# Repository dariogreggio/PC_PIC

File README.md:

# PC_PIC
a full computer made with Microchip PICs, featuring *everything*

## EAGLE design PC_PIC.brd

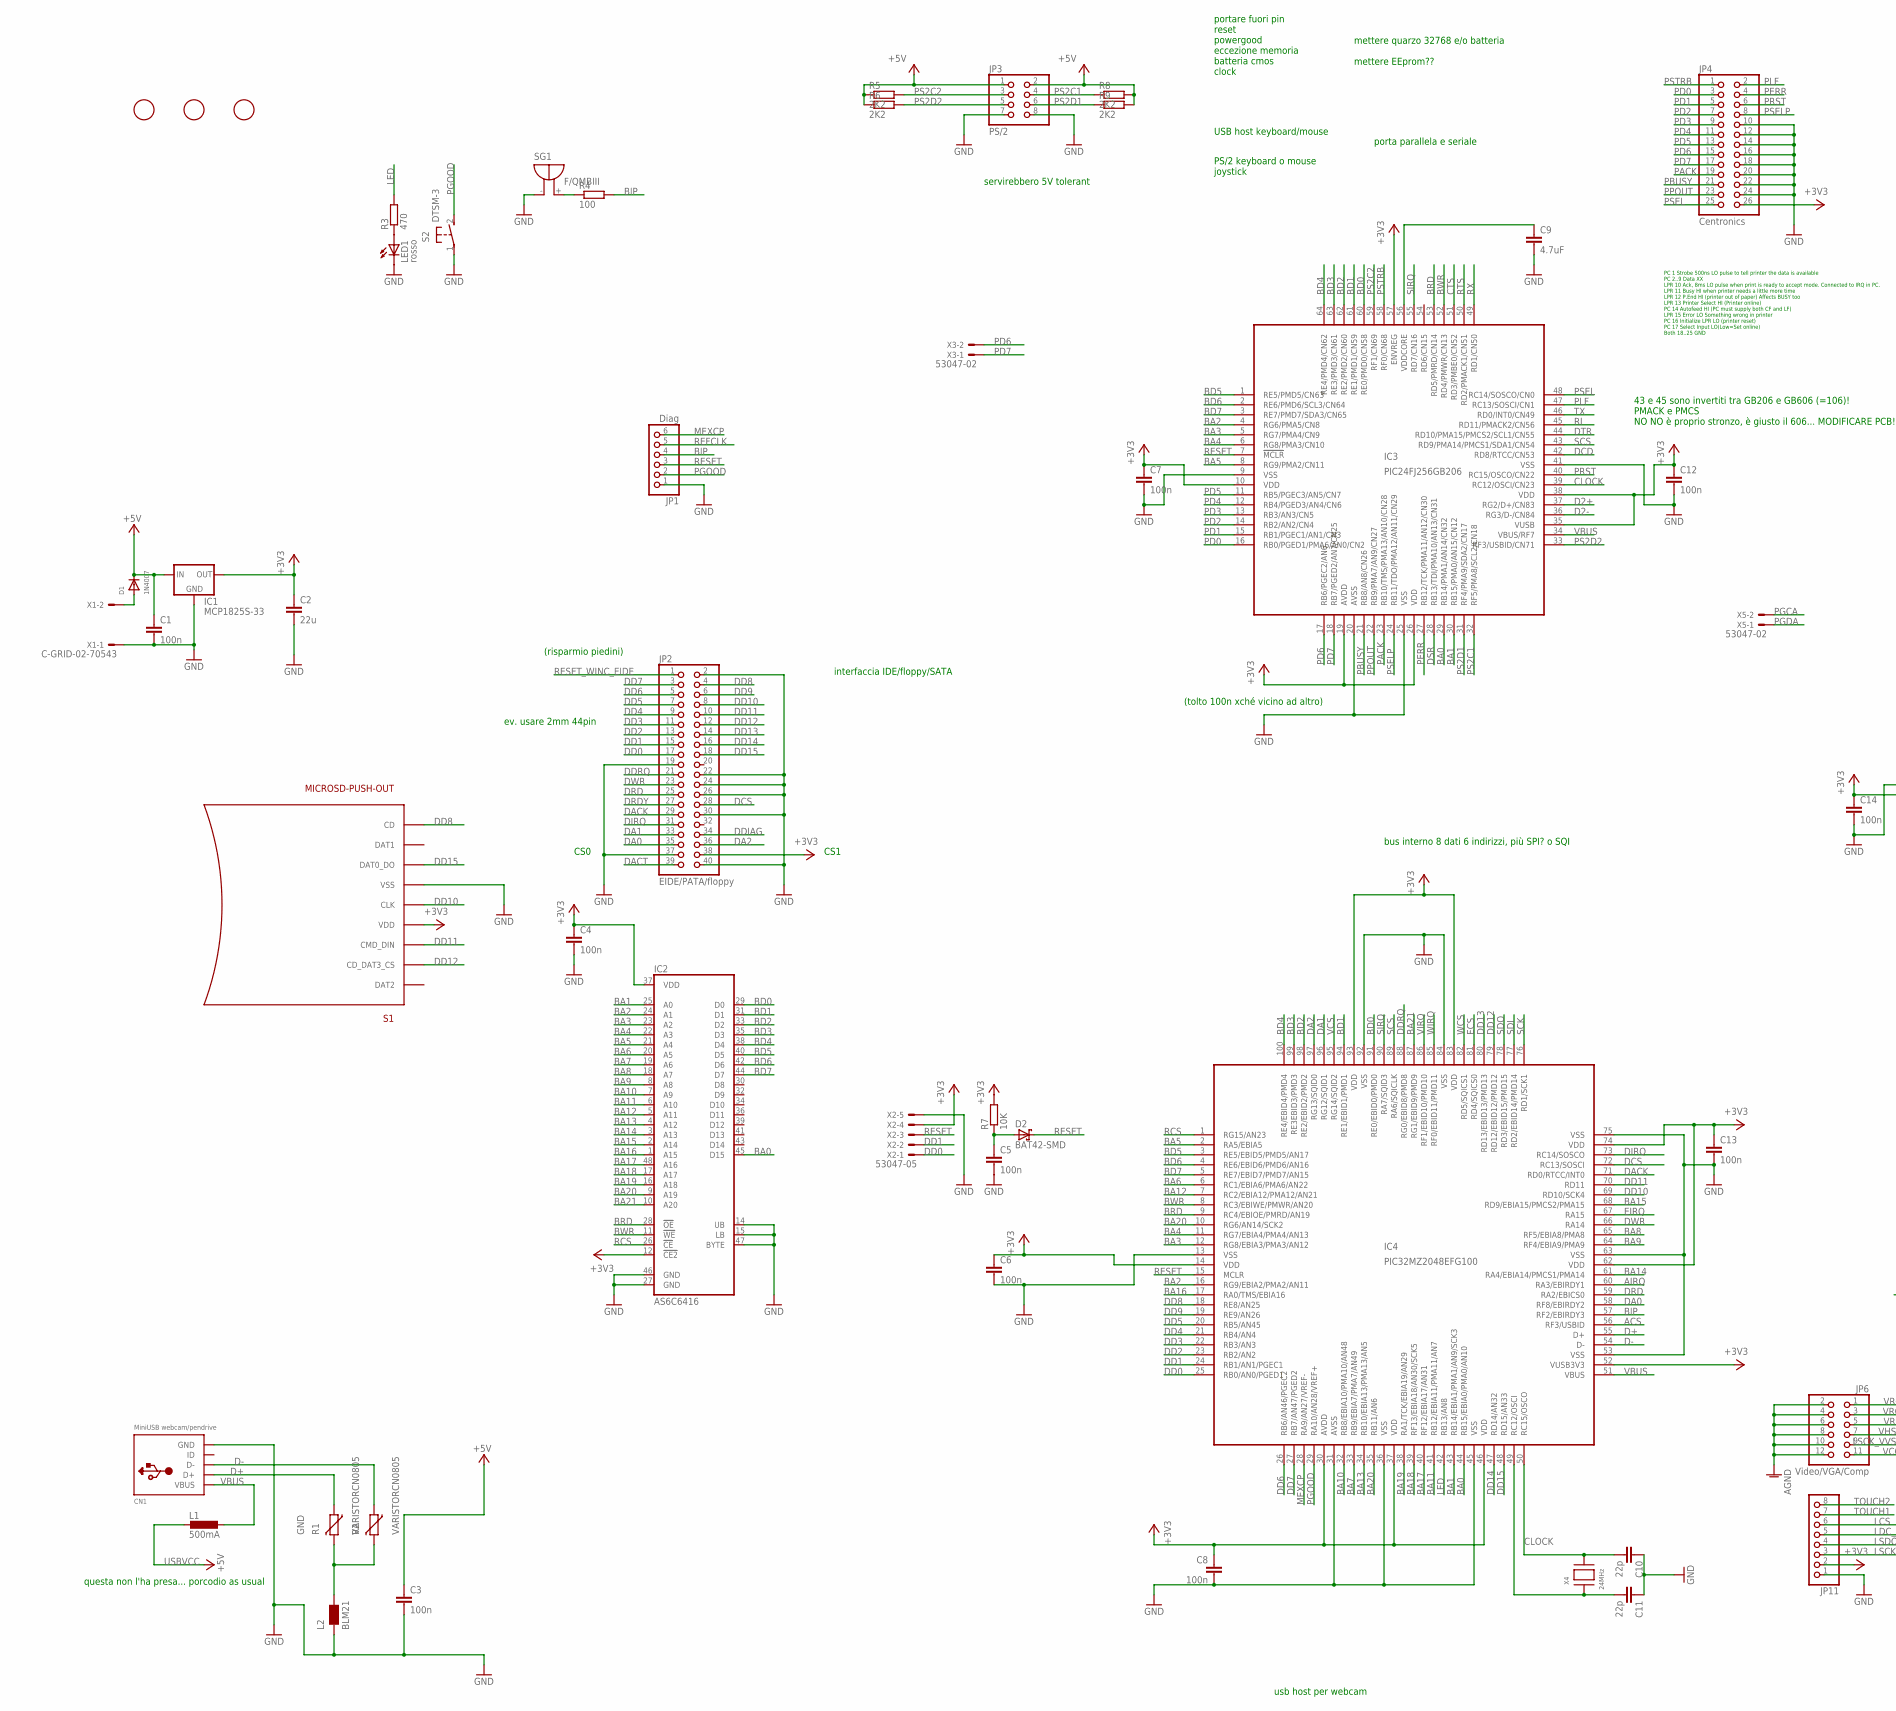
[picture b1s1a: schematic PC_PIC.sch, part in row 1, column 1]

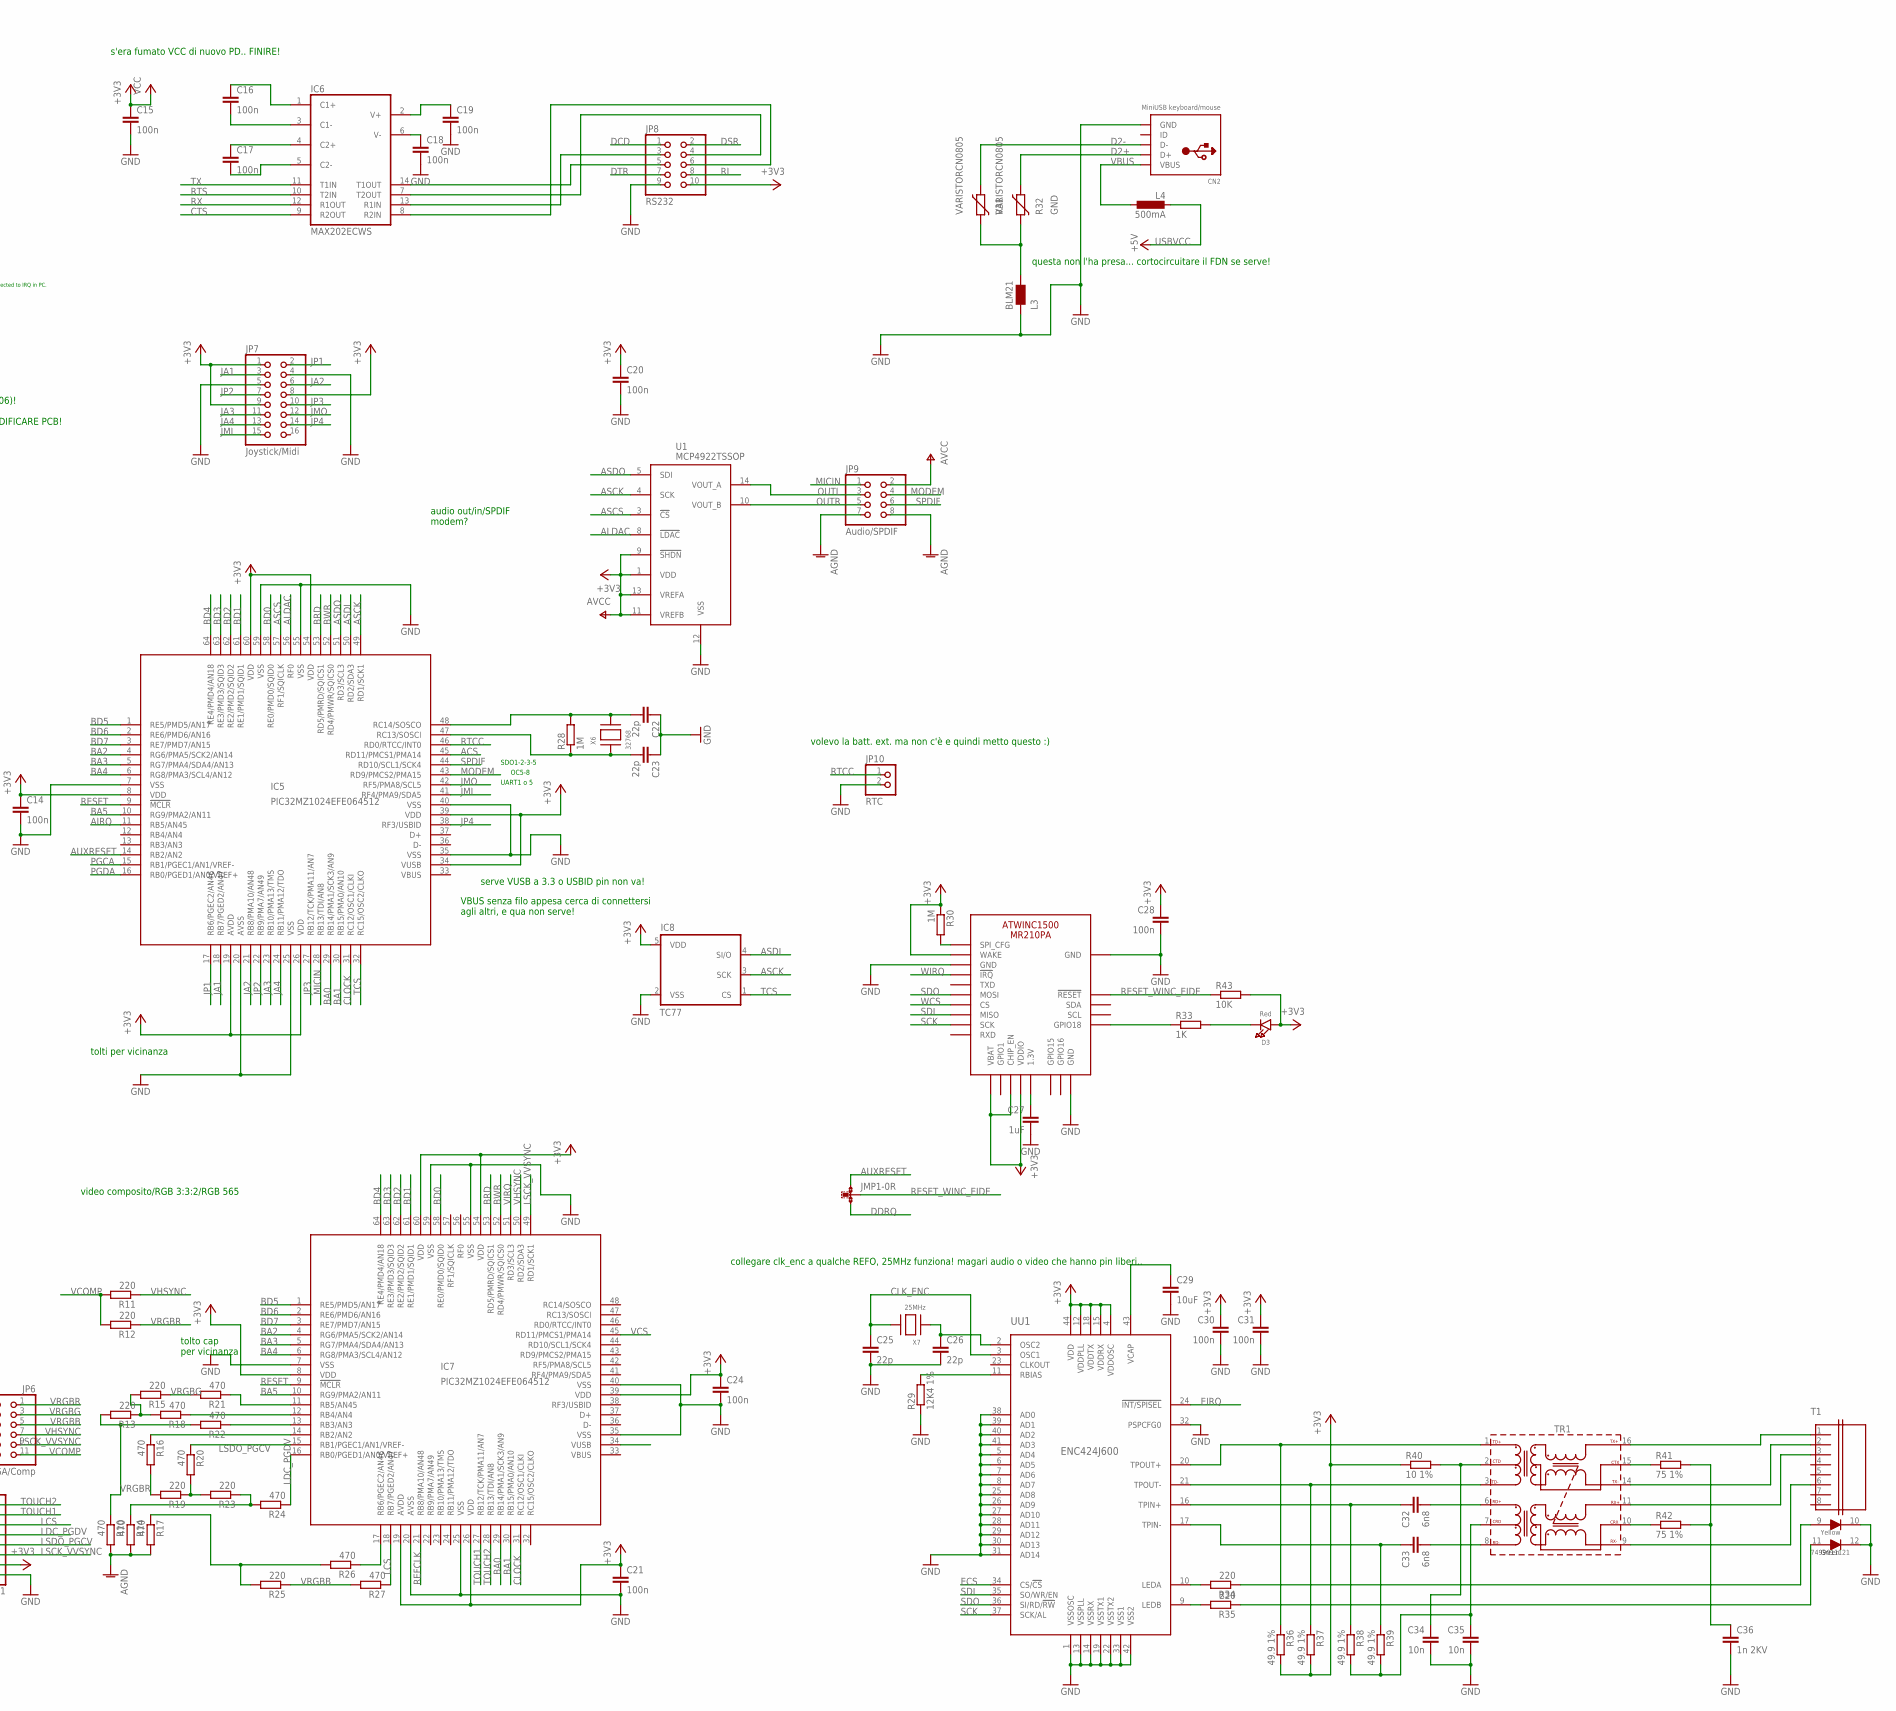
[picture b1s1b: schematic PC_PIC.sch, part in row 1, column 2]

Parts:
C1, C3, C4, C5, C6, C7, C8, C12, C13, C14, C15, C16, C17, C18, C19, C20, C21, C24, C28, C30, C31: 100n; C0805
C2: 22u; C1206
C9: 4.7uF; C1206
C10, C11, C22, C23, C25, C26: 22p; C0805
C27: 1uF; C0805
C29: 10uF; C1206
C32, C33: 6n8; C0805
C34, C35: 10n; C0805
C36: 1n 2KV; C1206
CN1: MiniUSB webcam/pendrive; USB-MINIB
CN2: MiniUSB keyboard/mouse; USB-MINIB
D1: 1N4007; SMADIODE
D2: BAT42-SMD; DO214AC
D3: Red; CHIPLED_0805_NOOUTLINE
F1, F2, F3: FIDUCIAL; FIDUCIAL_1MM
IC1: MCP1825S-33; SOT223
IC2: AS6C6416; TSOP48
IC3: PIC24FJ256GB206; TQFP64-10X10
IC4: PIC32MZ2048EFG100; TQFP100-14X14
IC5, IC7: PIC32MZ1024EFE064512; TQFP64-10X10
IC6: MAX202ECWS; SO16
IC8: TC77; SOT23-5L
JMP1: 0R-JUMPC; C0R-JMP
JP1: Diag; 1X06
JP2: EIDE/PATA/floppy; 2X20
JP3: PS/2; 2X04
JP4: Centronics; 2X13
JP6: Video/VGA/Comp; 2X06
JP7: Joystick/Midi; 2X08
JP8: RS232; 2X05
JP9: Audio/SPDIF; 2X04
JP10: RTC; 1X02
JP11: PINHD-1X08_2.54; 1X08
L1, L4: 500mA; L1812
L2, L3: BLM21; 0805
LED1: rosso; CHIPLED_0805
R1, R2, R31, R32: VARISTORCN0805; CT/CN0805
R3, R10, R14, R16, R17, R18, R20, R21, R22, R24, R26, R27: 470; R0805
R4: 100; R0805
R5, R6, R8, R9: 2K2; R0805
R7, R43: 10K; R0805
R11, R12, R13, R15, R19, R23, R25, R34, R35: 220; R0805
R28, R30: 1M; R0805
R29: 12K4 1%; R0805
R33: 1K; R0805
R36, R37, R38, R39: 49.9 1%; R0805
R40: 10 1%; R0805
R41, R42: 75 1%; R0805
S1: MICROSD-PUSH-OUT
S2: DTSM-3
SG1: F/QMBIII
T1: 7499011121; 01LAN_RJ45_10/00_Y-G_STD
TR1: WE-LAN-10/100-BASE-T,POE,749013011; 749013011
U1: MCP4922TSSOP; TSSOP14
UU1: ENC424J600; TQFP-44
X1: C-GRID-02-70543; 70543-02
X2: 53047-05
X3, X5: 53047-02
X4: 24MHz; NX5032
X6: 32768; XTAL3215
X7: 25MHz; NX5032
X8: ATWINC1500_MR210PB; ATWINC1500_MR210PA

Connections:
+3V3: C2.1, C4.1, C6.1, C7.1, C8.1, C12.1, C13.1, C14.1, C15.1, C20.1, C21.1, C24.1, C28.1, C30.1, C31.1, D3.A, IC1.3 (OUT), IC2.12 (!CE2), IC2.37 (VDD), IC3.10 (VDD), IC3.19 (AVDD), IC3.26 (VDD), IC3.35 (VUSB), IC3.38 (VDD), IC3.57 (ENVREG), IC4.14 (VDD), IC4.30 (AVDD), IC4.37 (VDD), IC4.46 (VDD), IC4.52 (VUSB3V3), IC4.62 (VDD), IC4.74 (VDD), IC4.83 (VDD), IC4.93 (VDD), IC5.8 (VDD), IC5.19 (AVDD), IC5.26 (VDD), IC5.34 (VUSB), IC5.39 (VDD), IC5.54 (VDD), IC5.60 (VDD), IC7.8 (VDD), IC7.19 (AVDD), IC7.26 (VDD), IC7.39 (VDD), IC7.54 (VDD), IC7.60 (VDD), IC8.5 (VDD), JP2.38, JP4.26, JP7.1, JP7.8, JP7.9, JP8.10, JP9.2, JP11.2, R7.2, R30.1, R36.2, R37.2, R40.1, R43.2, S1.4 (VDD), U1.1 (VDD), U1.9 (!SHDN), U1.11 (VREFB), U1.13 (VREFA), UU1.4 (VDDOSC), UU1.12 (VDDPLL), UU1.15 (VDDRX), UU1.18 (VDDTX), UU1.44 (VDD), X2.4, X8.J11 (WAKE), X8.J20 (VBAT), X8.J22 (CHIP_EN), X8.J23 (VDDIO)
+5V: C1.1, C3.1, D1.C, IC1.1 (IN), JP3.1, JP3.2, R5.1, R6.1, R8.2, R9.2
ACS: IC4.56 (RF3/USBID), IC5.45 (RD11/PMCS1/PMA14)
AIRQ: IC4.60 (RA3/EBIRDY1), IC5.11 (RB5/AN45)
ALDAC: IC5.56 (RF0), U1.8 (!LDAC)
ASCK: IC5.49 (RD1/SCK1), IC8.3 (SCK), U1.4 (SCK)
ASCS: IC5.57 (RF1/SQICLK), U1.3 (!CS)
ASDI: IC5.50 (RD2/SDA3), IC8.4 (SI/O)
ASDO: IC5.51 (RD3/SCL3), U1.5 (SDI)
AUXRESET: IC5.14 (RB2/AN2), JMP1.1
BA0: IC2.45 (D15), IC3.29 (RB14/PMA1/AN14/CN32), IC4.44 (RB15/EBIA0/PMA0/AN10), IC5.29 (RB14/PMA1/SCK3/AN9), IC7.29 (RB14/PMA1/SCK3/AN9)
BA1: IC2.25 (A0), IC3.30 (RB15/PMA0/AN15/CN12), IC4.43 (RB14/EBIA1/PMA1/AN9/SCK3), IC5.30 (RB15/PMA0/AN10), IC7.30 (RB15/PMA0/AN10)
BA2: IC2.24 (A1), IC3.4 (RG6/PMA5/CN8), IC4.16 (RG9/EBIA2/PMA2/AN11), IC5.4 (RG6/PMA5/SCK2/AN14), IC7.4 (RG6/PMA5/SCK2/AN14)
BA3: IC2.23 (A2), IC3.5 (RG7/PMA4/CN9), IC4.12 (RG8/EBIA3/PMA3/AN12), IC5.5 (RG7/PMA4/SDA4/AN13), IC7.5 (RG7/PMA4/SDA4/AN13)
BA4: IC2.22 (A3), IC3.6 (RG8/PMA3/CN10), IC4.11 (RG7/EBIA4/PMA4/AN13), IC5.6 (RG8/PMA3/SCL4/AN12), IC7.6 (RG8/PMA3/SCL4/AN12)
BA5: IC2.21 (A4), IC3.8 (RG9/PMA2/CN11), IC4.2 (RA5/EBIA5), IC5.10 (RG9/PMA2/AN11), IC7.10 (RG9/PMA2/AN11)
BA6: IC2.20 (A5), IC4.6 (RC1/EBIA6/PMA6/AN22)
BA7: IC2.19 (A6), IC4.33 (RB9/EBIA7/PMA7/AN49)
BA8: IC2.18 (A7), IC4.65 (RF5/EBIA8/PMA8)
BA9: IC2.8 (A8), IC4.64 (RF4/EBIA9/PMA9)
BA10: IC2.7 (A9), IC4.32 (RB8/EBIA10/PMA10/AN48)
BA11: IC2.6 (A10), IC4.41 (RB12/EBIA11/PMA11/AN7)
BA12: IC2.5 (A11), IC4.7 (RC2/EBIA12/PMA12/AN21)
BA13: IC2.4 (A12), IC4.34 (RB10/EBIA13/PMA13/AN5)
BA14: IC2.3 (A13), IC4.61 (RA4/EBIA14/PMCS1/PMA14)
BA15: IC2.2 (A14), IC4.68 (RD9/EBIA15/PMCS2/PMA15)
BA16: IC2.1 (A15), IC4.17 (RA0/TMS/EBIA16)
BA17: IC2.48 (A16), IC4.40 (RF12/EBIA17/AN31)
BA18: IC2.17 (A17), IC4.39 (RF13/EBIA18/AN30/SCK5)
BA19: IC2.16 (A18), IC4.38 (RA1/TCK/EBIA19/AN29)
BA20: IC2.9 (A19), IC4.10 (RG6/AN14/SCK2), IC4.35 (RB11/AN6)
BA21: IC2.10 (A20), IC4.87 (RG1/EBID9/PMD9)
BD0: IC2.29 (D0), IC3.60 (RE0/PMD0/CN58), IC4.91 (RE0/EBID0/PMD0), IC5.58 (RE0/PMD0/SQID0), IC7.58 (RE0/PMD0/SQID0)
BD1: IC2.31 (D1), IC3.61 (RE1/PMD1/CN59), IC4.94 (RE1/EBID1/PMD1), IC5.61 (RE1/PMD1/SQID1), IC7.61 (RE1/PMD1/SQID1)
BD2: IC2.33 (D2), IC3.62 (RE2/PMD2/CN60), IC4.98 (RE2/EBID2/PMD2), IC5.62 (RE2/PMD2/SQID2), IC7.62 (RE2/PMD2/SQID2)
BD3: IC2.35 (D3), IC3.63 (RE3/PMD3/CN61), IC4.99 (RE3EBID3/PMD3), IC5.63 (RE3/PMD3/SQID3), IC7.63 (RE3/PMD3/SQID3)
BD4: IC2.38 (D4), IC3.64 (RE4/PMD4/CN62), IC4.100 (RE4/EBID4/PMD4), IC5.64 (RE4/PMD4/AN18), IC7.64 (RE4/PMD4/AN18)
BD5: IC2.40 (D5), IC3.1 (RE5/PMD5/CN63), IC4.3 (RE5/EBID5/PMD5/AN17), IC5.1 (RE5/PMD5/AN17), IC7.1 (RE5/PMD5/AN17)
BD6: IC2.42 (D6), IC3.2 (RE6/PMD6/SCL3/CN64), IC4.4 (RE6/EBID6/PMD6/AN16), IC5.2 (RE6/PMD6/AN16), IC7.2 (RE6/PMD6/AN16)
BD7: IC2.44 (D7), IC3.3 (RE7/PMD7/SDA3/CN65), IC4.5 (RE7/EBID7/PMD7/AN15), IC5.3 (RE7/PMD7/AN15), IC7.3 (RE7/PMD7/AN15)
BIP: IC4.57 (RF2/EBIRDY3), JP1.4, R4.2
BRD: IC2.28 (!OE), IC3.53 (RD5/PMRD/CN14), IC4.9 (RC4/EBIOE/PMRD/AN19), IC5.53 (RD5/PMRD/SQICS1), IC7.53 (RD5/PMRD/SQICS1)
BWR: IC2.11 (!WE), IC3.52 (RD4/PMWR/CN13), IC4.8 (RC3/EBIWE/PMWR/AN20), IC5.52 (RD4/PMWR/SQICS0), IC7.52 (RD4/PMWR/SQICS0)
CLK_ENC: C25.1, UU1.3 (OSC1), X7.P$2
CLOCK: C10.2, IC3.39 (RC12/OSCI/CN23), IC4.50 (RC15/OSCO), IC5.31 (RC12/OSC1/CLKI), IC7.31 (RC12/OSC1/CLKI), X4.P$2
CTS: IC3.51 (RD3/PMBE0/CN52), IC6.9 (R2OUT)
D2+: CN2.D+, IC3.37 (RG2/D+/CN83), R32.1
D2-: CN2.D-, IC3.36 (RG3/D-/CN84), R31.1
D+: CN1.D+, IC4.55 (D+), R1.1
D-: CN1.D-, IC4.54 (D-), R2.1
DA0: IC4.58 (RF8/EBIRDY2), JP2.35
DA1: IC4.96 (RG12/SQID1), JP2.33
DA2: IC4.97 (RG13/SQID0), JP2.36
DACK: IC4.71 (RD0/RTCC/INT0), JP2.29
DACT: JP2.39
DCD: IC3.42 (RD8/RTCC/CN53), JP8.1
DCS: IC4.72 (RC13/SOSCI), JP2.28
DD0: IC4.25 (RB0/AN0/PGED1), JP2.17, X2.1
DD1: IC4.24 (RB1/AN1/PGEC1), JP2.15, X2.2
DD2: IC4.23 (RB2/AN2), JP2.13
DD3: IC4.22 (RB3/AN3), JP2.11
DD4: IC4.21 (RB4/AN4), JP2.9
DD5: IC4.20 (RB5/AN45), JP2.7
DD6: IC4.26 (RB6/AN46/PGEC2), JP2.5
DD7: IC4.27 (RB7/AN47/PGED2), JP2.3
DD8: IC4.18 (RE8/AN25), JP2.4, S1.CD
DD9: IC4.19 (RE9/AN26), JP2.6
DD10: IC4.69 (RD10/SCK4), JP2.8, S1.5 (CLK)
DD11: IC4.70 (RD11), JP2.10, S1.3 (CMD_DIN)
DD12: IC4.79 (RD12/EBID12/PMD12), JP2.12, S1.2 (CD_DAT3_CS)
DD13: IC4.80 (RD13/EBID13/PMD13), JP2.14
DD14: IC4.47 (RD14/AN32), JP2.16
DD15: IC4.48 (RD15/AN33), JP2.18, S1.7 (DAT0_DO)
DDIAG: JP2.34
DDRQ: IC4.88 (RG0/EBID8/PMD8), JMP1.3, JP2.21
DIRQ: IC4.73 (RC14/SOSCO), JP2.31
DRD: IC4.59 (RA2/EBICS0), JP2.25
DRDY: JP2.27
DSR: IC3.28 (RB13/TDI/PMA10/AN13/CN31), JP8.2
DTR: IC3.44 (RD10/PMA15/PMCS2/SCL1/CN55), JP8.7
DWR: IC4.66 (RA14), JP2.23
ECS: IC4.81 (RD4/SQICS0), UU1.34 (CS/!CS)
EIRQ: IC4.67 (RA15), UU1.24 (!INT/SPISEL)
GND: C1.2, C2.2, C3.2, C4.2, C5.2, C6.2, C7.2, C8.2, C9.2, C10.1, C11.1, C12.2, C13.2, C14.2, C15.2, C18.2, C19.2, C20.2, C21.2, C22.1, C23.1, C24.2, C25.2, C26.2, C27.2, C28.2, C29.2, C30.2, C31.2, C34.2, C35.2, C36.2, CN1.GND, CN2.GND, IC1.2 (GND), IC1.4 (GND), IC2.14 (UB), IC2.15 (LB), IC2.27 (GND), IC2.46 (GND), IC2.47 (BYTE), IC3.9 (VSS), IC3.20 (AVSS), IC3.25 (VSS), IC3.41 (VSS), IC4.13 (VSS), IC4.31 (AVSS), IC4.36 (VSS), IC4.45 (VSS), IC4.53 (VSS), IC4.63 (VSS), IC4.75 (VSS), IC4.84 (VSS), IC4.92 (VSS), IC5.7 (VSS), IC5.20 (AVSS), IC5.25 (VSS), IC5.35 (VSS), IC5.40 (VSS), IC5.55 (VSS), IC5.59 (VSS), IC6.15 (GND), IC7.7 (VSS), IC7.20 (AVSS), IC7.25 (VSS), IC7.35 (VSS), IC7.40 (VSS), IC7.55 (VSS), IC7.59 (VSS), IC8.2 (VSS), JP1.1, JP2.2, JP2.19, JP2.22, JP2.24, JP2.26, JP2.30, JP2.37, JP2.40, JP3.7, JP3.8, JP4.10, JP4.12, JP4.14, JP4.16, JP4.18, JP4.20, JP4.22, JP4.24, JP6.2, JP6.4, JP6.6, JP6.8, JP6.10, JP6.12, JP7.4, JP7.5, JP8.9, JP9.7, JP9.8, JP10.2, JP11.1, L2.1, L3.1, LED1.C, R10.2, R14.2, R17.2, R29.1, S1.6 (VSS), S1.G1 (VSS), S1.G2 (VSS), S1.G3 (VSS), S1.G4 (VSS), S2.1, SG1.- (+), T1.10, T1.12, U1.12 (VSS), UU1.1 (VSSOSC), UU1.5 (AD4), UU1.6 (AD5), UU1.7 (AD6), UU1.8 (AD7), UU1.13 (VSSPLL), UU1.14 (VSSRX), UU1.19 (VSSTX1), UU1.22 (VSSTX2), UU1.25 (AD8), UU1.26 (AD9), UU1.27 (AD10), UU1.28 (AD11), UU1.29 (AD12), UU1.30 (AD13), UU1.31 (AD14), UU1.32 (PSPCFG0), UU1.33 (VSS1), UU1.38 (AD0), UU1.39 (AD1), UU1.40 (AD2), UU1.41 (AD3), UU1.42 (VSS2), X1.1, X2.5, X8.J9 (GND), X8.J12 (GND), X8.J28 (GND), X8.MTGND (GND)
JA1: IC5.18 (RB7/PGED2/AN47), JP7.3
JA2: IC5.21 (RB8/PMA10/AN48), JP7.6
JA3: IC5.23 (RB10/PMA13/TMS), JP7.11
JA4: IC5.24 (RB11/PMA12/TDO), JP7.13
JMI: IC5.41 (RF4/PMA9/SDA5), JP7.15
JMO: IC5.42 (RF5/PMA8/SCL5), JP7.12
JP1: IC5.17 (RB6/PGEC2/AN46), JP7.2
JP2: IC5.22 (RB9/PMA7/AN49), JP7.7
JP3: IC5.27 (RB12/TCK/PMA11/AN7), JP7.10
JP4: IC5.38 (RF3/USBID), JP7.14
LCS: IC7.18 (RB7/PGED2/AN47), JP11.6, R27.1
LDC_PGDV: IC7.16 (RB0/PGED1/AN0/VREF+), JP11.5, R24.1
LED: IC4.42 (RB13/AN8), R3.2
LSCK_VVSYNC: IC7.49 (RD1/SCK1), JP6.9, JP11.3
LSDO_PGCV: IC7.15 (RB1/PGEC1/AN1/VREF-), JP11.4, R20.1
MEXCP: IC4.28 (RA9/AN27/VREF-), JP1.6
MICIN: IC5.28 (RB13/TDI/AN8), JP9.1
MODEM: IC5.43 (RD9/PMCS2/PMA15), JP9.4
unnamed: C32.2, TR1.6 (RD+)
unnamed: R36.1, TR1.1 (TD+), UU1.20 (TPOUT+)
unnamed: C16.2, IC6.3 (C1-)
unnamed: C5.1, D2.A, R7.1
unnamed: D1.A, X1.2
unnamed: LED1.A, R3.1
unnamed: C16.1, IC6.1 (C1+)
unnamed: R37.1, TR1.3 (TD-), UU1.21 (TPOUT-)
unnamed: R4.1, SG1.+ (-)
unnamed: C32.1, R38.1, UU1.16 (TPIN+)
unnamed: IC7.17 (RB6/PGEC2/AN46), R26.1
unnamed: C34.1, R40.2, TR1.2 (CTD)
unnamed: C33.1, R39.1, UU1.17 (TPIN-)
unnamed: C17.1, IC6.4 (C2+)
unnamed: IC7.14 (RB2/AN2), R16.1
unnamed: R33.1, X8.J1 (GPIO18)
unnamed: D3.C, R33.2
unnamed: IC7.11 (RB5/AN45), R21.1
unnamed: C11.2, IC4.49 (RC12/OSCI), X4.P$1
unnamed: C27.1, X8.J24 (1.3V)
unnamed: R30.2, X8.J10 (SPI_CFG)
unnamed: C26.1, UU1.2 (OSC2), X7.P$1
unnamed: IC7.12 (RB4/AN4), R18.1
unnamed: R29.2, UU1.11 (RBIAS)
unnamed: C17.2, IC6.5 (C2-)
unnamed: R35.1, T1.11
unnamed: C29.1, UU1.43 (VCAP)
unnamed: R34.2, UU1.10 (LEDA)
unnamed: R35.2, UU1.9 (LEDB)
unnamed: T1.1, TR1.16 (TX+)
unnamed: T1.2, TR1.14 (TX-)
unnamed: T1.3, TR1.11 (RX+)
unnamed: C19.1, IC6.2 (V+)
unnamed: C18.1, IC6.6 (V-)
unnamed: T1.6, TR1.9 (RX-)
unnamed: R34.1, T1.9
unnamed: IC6.14 (T1OUT), JP8.5
unnamed: IC6.7 (T2OUT), JP8.4
unnamed: C33.2, TR1.8 (RD-)
unnamed: C35.1, R38.2, R39.2, TR1.7 (CRD)
unnamed: R41.1, TR1.15 (CTX)
unnamed: R42.1, TR1.10 (CRX)
unnamed: C36.1, R41.2, R42.2
unnamed: IC6.13 (R1IN), JP8.3
unnamed: IC6.8 (R2IN), JP8.6
unnamed: C9.1, IC3.56 (VDDCORE)
unnamed: IC7.13 (RB3/AN3), R22.1
unnamed: R17.1, R25.2, R26.2
unnamed: R10.1, R13.2, R22.2
unnamed: R19.1, R20.2, R23.2
unnamed: R14.1, R23.1, R24.2
unnamed: R13.1, R15.2, R18.2
OUTL: JP9.3, U1.14 (VOUT_A)
OUTR: JP9.5, U1.10 (VOUT_B)
PACK: IC3.23 (RB10/TMS/PMA13/AN10/CN28), JP4.19
PBUSY: IC3.21 (RB8/AN8/CN26), JP4.21
PD0: IC3.16 (RB0/PGED1/PMA6/AN0/CN2), JP4.3
PD1: IC3.15 (RB1/PGEC1/AN1/CN3), JP4.5
PD2: IC3.14 (RB2/AN2/CN4), JP4.7
PD3: IC3.13 (RB3/AN3/CN5), JP4.9
PD4: IC3.12 (RB4/PGED3/AN4/CN6), JP4.11
PD5: IC3.11 (RB5/PGEC3/AN5/CN7), JP4.13
PD6: IC3.17 (RB6/PGEC2/AN6), JP4.15, X3.2
PD7: IC3.18 (RB7/PGED2/AN7/CN25), JP4.17, X3.1
PERR: IC3.27 (RB12/TCK/PMA11/AN12/CN30), JP4.4
PGCA: IC5.15 (RB1/PGEC1/AN1/VREF-), X5.2
PGDA: IC5.16 (RB0/PGED1/AN0/VREF+), X5.1
PGOOD: IC4.29 (RA10/AN28/VREF+), JP1.2, S2.2
PLF: IC3.47 (RC13/SOSCI/CN1), JP4.2
PPOUT: IC3.22 (RB9/PMA7/AN9/CN27), JP4.23
PRST: IC3.40 (RC15/OSCO/CN22), JP4.6
PS2C1: IC3.32 (RF5/PMA8/SCL2/CN18), JP3.4, R8.1
PS2C2: IC3.59 (RF1/CN69), JP3.3, R5.2
PS2D1: IC3.31 (RF4/PMA9/SDA2/CN17), JP3.6, R9.1
PS2D2: IC3.33 (RF3/USBID/CN71), JP3.5, R6.2
PSEL: IC3.48 (RC14/SOSCO/CN0), JP4.25
PSELP: IC3.24 (RB11/TDO/PMA12/AN11/CN29), JP4.8
PSTRB: IC3.58 (RF0/CN68), JP4.1
RCS: IC2.26 (!CE), IC4.1 (RG15/AN23)
REFCLK: IC7.21 (RB8/PMA10/AN48), JP1.5
RESET: D2.C, IC3.7 (!MCLR), IC4.15 (MCLR), IC5.9 (!MCLR), IC7.9 (!MCLR), JP1.3, X2.3
RESET_WINC_EIDE: JMP1.2, JP2.1, R43.1, X8.J4 (!RESET)
RI: IC3.45 (RD11/PMACK2/CN56), JP8.8
RTCC: IC5.46 (RD0/RTCC/INT0), JP10.1
RTS: IC3.50 (RD2/PMACK1/CN51), IC6.10 (T2IN)
RX: IC3.49 (RD1/CN50), IC6.12 (R1OUT)
SCK: IC4.76 (RD1/SCK1), UU1.37 (SCK/AL), X8.J18 (SCK)
SCS: IC3.43 (RD9/PMA14/PMCS1/SDA1/CN54), IC4.89 (RA6/SQICLK)
SDI: IC4.77 (RD2/EBID14/PMD14), UU1.35 (SO/WR/EN), X8.J17 (MISO)
SDO: IC4.78 (RD3/EBID15/PMD15), UU1.36 (SI/RD/!RW), X8.J15 (MOSI)
SIRQ: IC3.55 (RD7/CN16), IC4.90 (RA7/SQID3)
SOSCI: C23.2, IC5.47 (RC13/SOSCI), R28.1, X6.P$1
SOSCO: C22.2, IC5.48 (RC14/SOSCO), R28.2, X6.P$2
SPDIF: IC5.44 (RD10/SCL1/SCK4), JP9.6
TCS: IC5.32 (RC15/OSC2/CLKO), IC8.1 (CS)
TOUCH1: IC7.27 (RB12/TCK/PMA11/AN7), JP11.7
TOUCH2: IC7.28 (RB13/TDI/AN8), JP11.8
TX: IC3.46 (RD0/INT0/CN49), IC6.11 (T1IN)
USBVCC: L1.2, L4.2
USHIELD: L2.2, R1.2, R2.2
USHIELD1: L3.2, R31.2, R32.2
VBUS: CN1.VBUS, CN2.VBUS, IC3.34 (VBUS/RF7), IC4.51 (VBUS), L1.1, L4.1
VCC: IC6.16 (VCC)
VCOMP: JP6.11, R11.2, R12.2
VCS: IC4.95 (RG14/SQID2), IC7.45 (RD11/PMCS1/PMA14)
VHSYNC: IC7.50 (RD2/SDA3), JP6.7, R11.1
VIRQ: IC4.86 (RF1/EBID10/PMD10), IC7.51 (RD3/SCL3)
VRGBB: JP6.5, R25.1, R27.2
VRGBG: JP6.3, R15.1, R21.2
VRGBR: JP6.1, R12.1, R16.2, R19.2
WCS: IC4.82 (RD5/SQICS1), X8.J16 (CS)
WIRQ: IC4.85 (RF0/EBID11/PMD11), X8.J13 (!IRQ)

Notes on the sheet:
questa non l'ha presa... porcodio as usual
video composito/RGB 3:3:2/RGB 565
usb host per webcam
USB host keyboard/mouse
PS/2 keyboard o mouse joystick
audio out/in/SPDIF modem?
interfaccia IDE/floppy/SATA
bus interno 8 dati 6 indirizzi, più SPI? o SQI
porta parallela e seriale
questa non l'ha presa... cortocircuitare il FDN se serve!
portare fuori pin reset powergood eccezione memoria batteria cmos clock
mettere quarzo 32768 e/o batteria mettere EEprom??
(risparmio piedini)
servirebbero 5V tolerant
PC 1 Strobe 500ns LO pulse to tell printer the data is available PC 2..9 Data XX LPR 10 Ack, 8ms LO pulse when print is ready to accept mode. Connected to IRQ in PC. LPR 11 Busy HI when printer needs a little more time LPR 12 P.End HI (printer out of paper) Affects BUSY too LPR 13 Printer Select HI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
volevo la batt. ext. ma non c'è e quindi metto questo :)
ev. usare 2mm 44pin
(tolto 100n xché vicino ad altro)
tolto cap per vicinanza
tolti per vicinanza
serve VUSB a 3.3 o USBID pin non va!
UART1 o 5
SDO1-2-3-5
OC5-8
CS1
CS0
s'era fumato VCC di nuovo PD.. FINIRE!
43 e 45 sono invertiti tra GB206 e GB606 (=106)! PMACK e PMCS NO NO è proprio stronzo, è giusto il 606... MODIFICARE PCB!
VBUS senza filo appesa cerca di connettersi agli altri, e qua non serve!
collegare clk_enc a qualche REFO, 25MHz funziona! magari audio o video che hanno pin liberi..

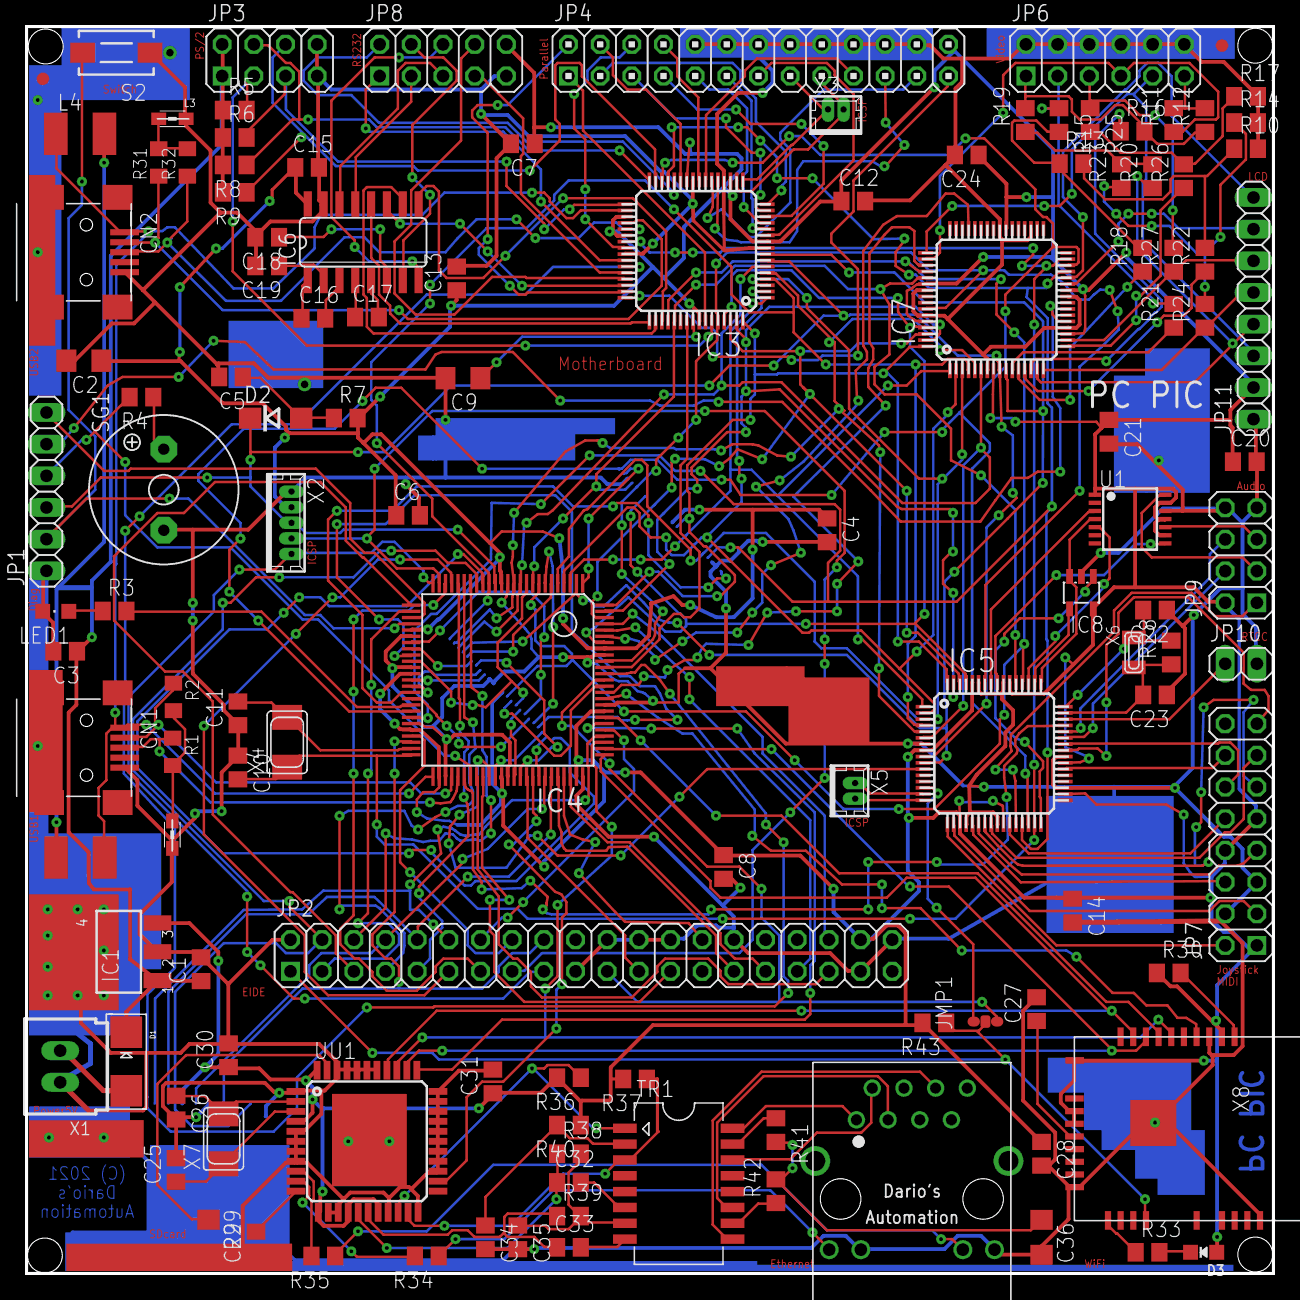
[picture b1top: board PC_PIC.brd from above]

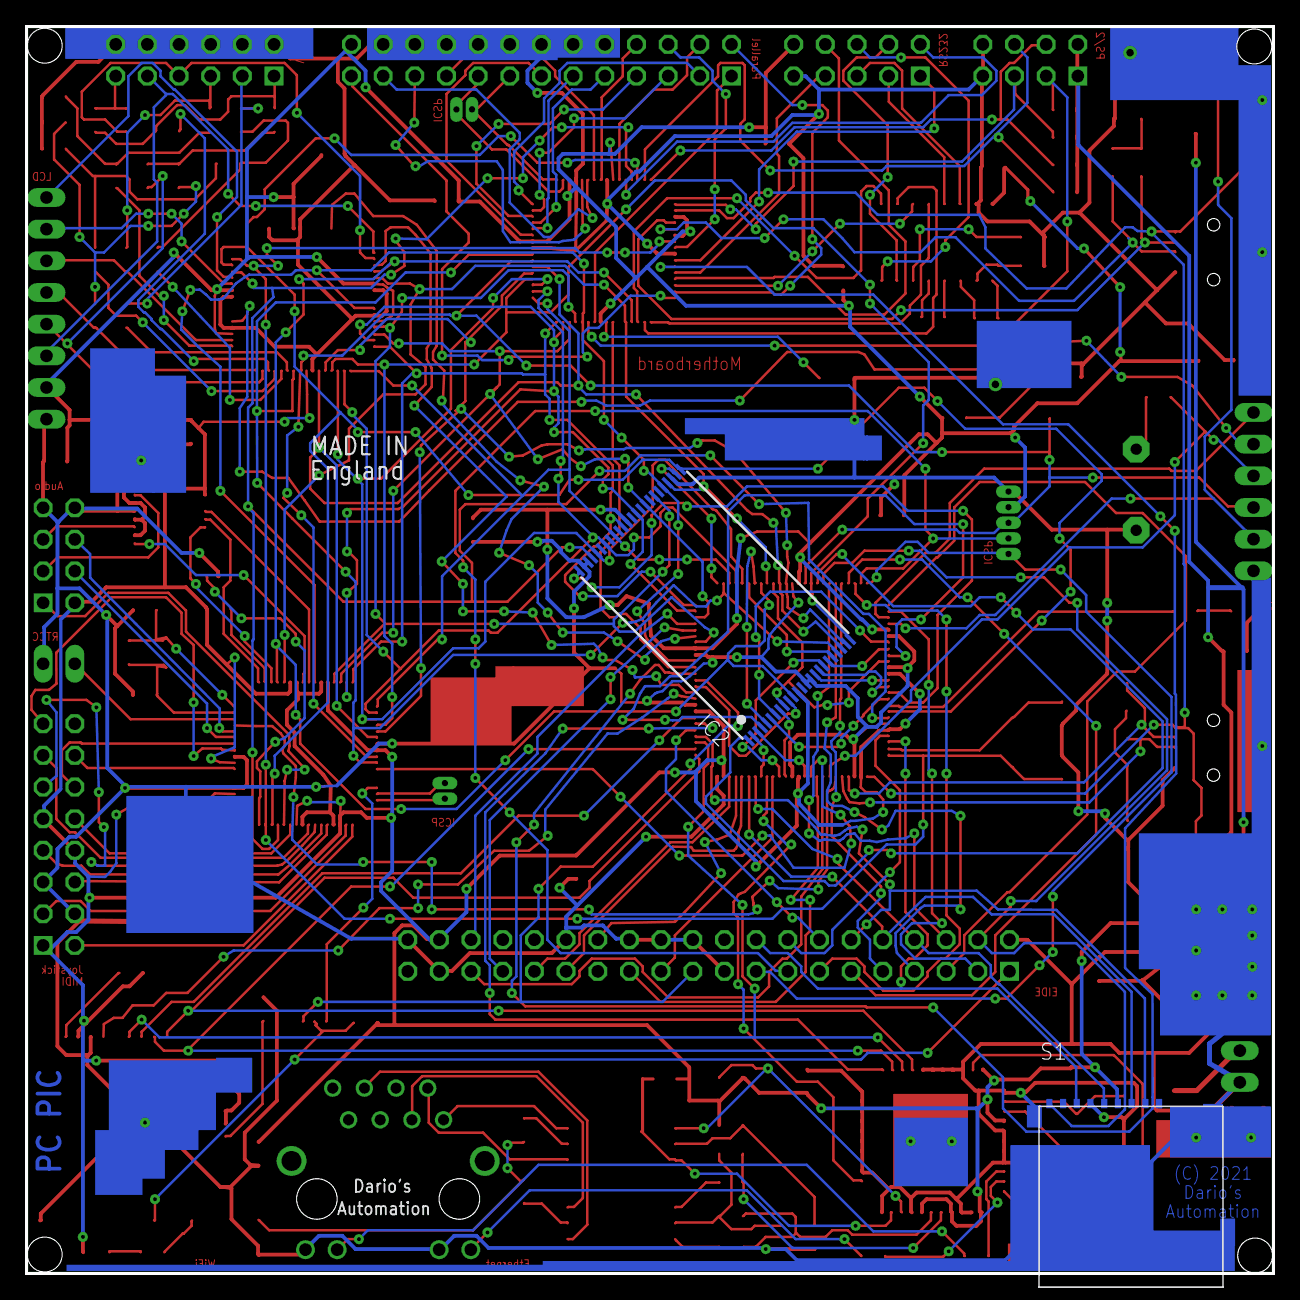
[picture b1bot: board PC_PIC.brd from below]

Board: 2 copper layers, 100.0 x 100.0 mm, 126 parts (2 on the bottom side), 210 nets.

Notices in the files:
PC_PIC.brd:
(C) 2021
parts and their libraries:
microbuilder: This work is placed in the public domain, and may be freely used for commercial and non-commercial work with the following conditions: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
wurth_electronics_midcom_inc_v1-0: Copyright: Wurth Electronics Midcom, Inc.
